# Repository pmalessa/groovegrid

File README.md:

# README #

GrooveGrid WS2812b Controller

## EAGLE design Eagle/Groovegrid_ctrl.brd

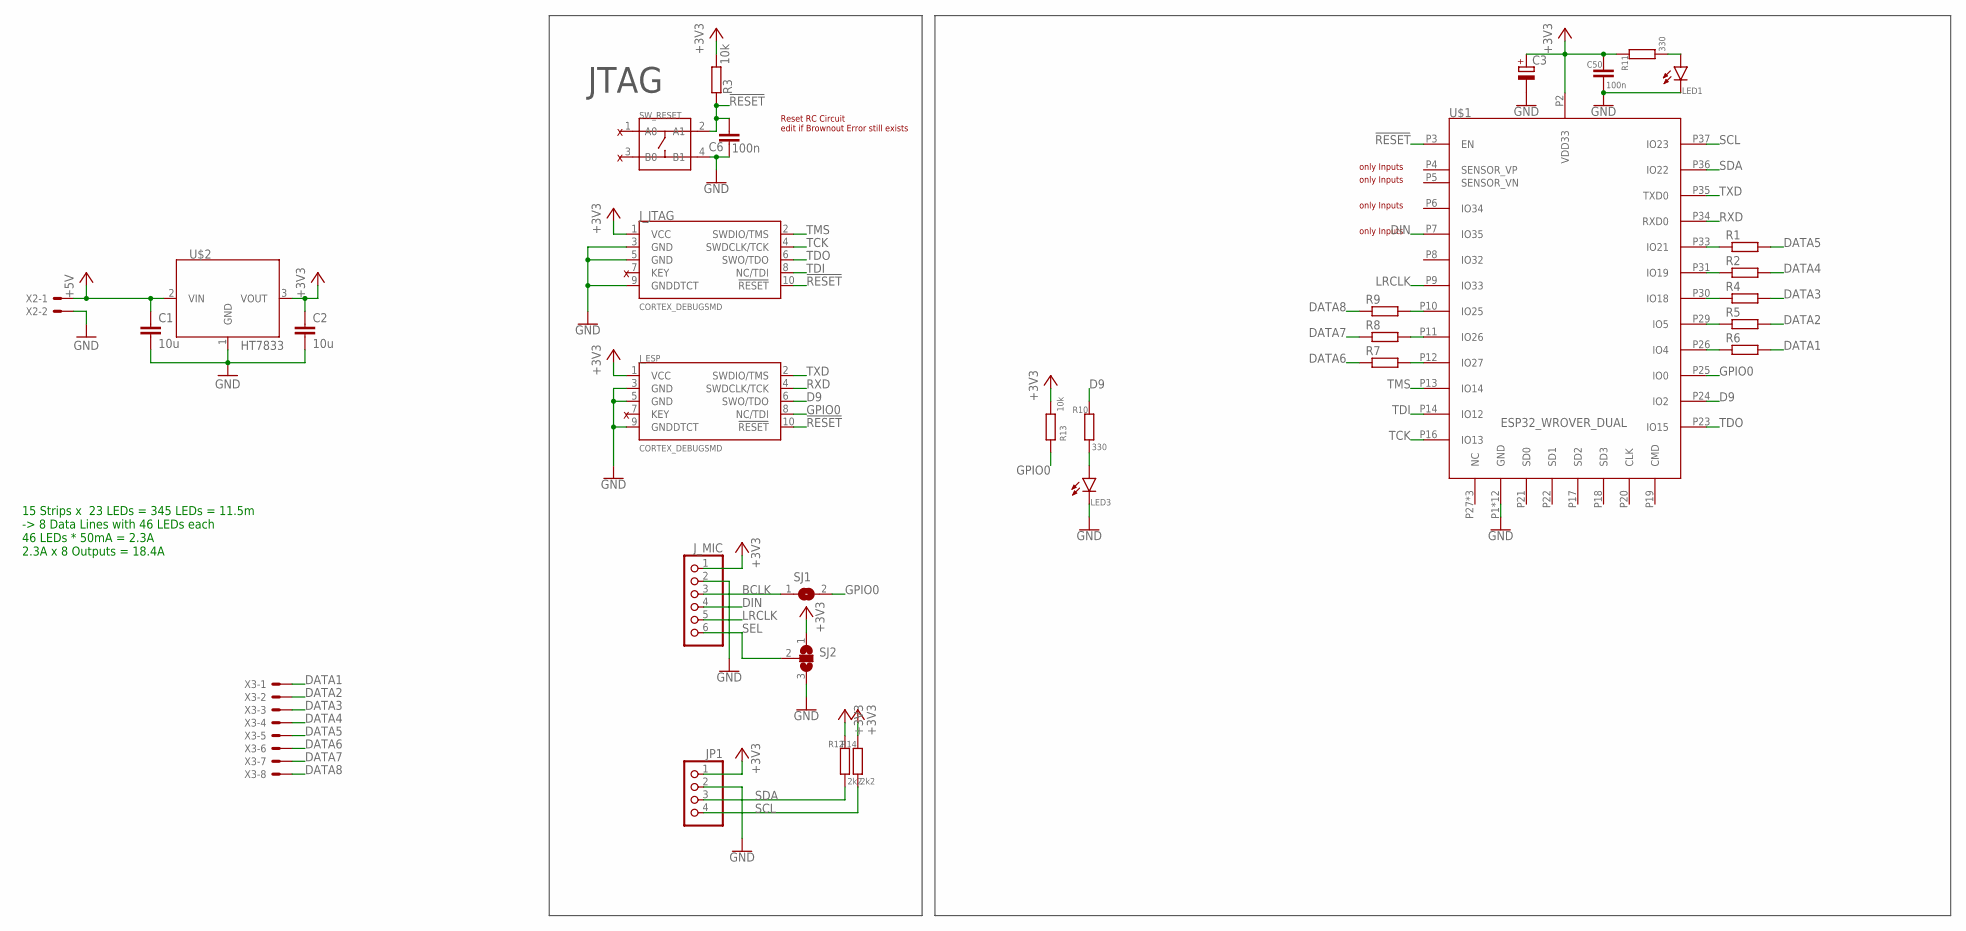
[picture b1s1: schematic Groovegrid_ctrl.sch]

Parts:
C1, C2: 10u; C0805
C3: CPOL-EUD; PANASONIC_D
C6, C50: 100n; C0805K
JP1: PINHD-1X4; 1X04
J_ESP: CORTEX_DEBUGSMD; 2X5_FTSH-105
J_JTAG: CORTEX_DEBUGSMD; 2X5_FTSH-105
J_MIC: PINHD-1X6; 1X06
LED1, LED3: LEDCHIPLED_0805; CHIPLED_0805
R1, R2, R4, R5, R6, R7, R8, R9: R-EU_R0805; R0805
R3, R13: 10k; R0805
R10, R11: 330; R0805
R12, R14: 2k2; R0805
SJ1: SJ
SJ2: SJ2W; SJ_2
SW_RESET: SKQGADE010; SW_4P-5.2X5.2X1.5MM
U$1: ESP32_WROVER_DUAL; ESP32_WROVER
U$2: HT7833; SOT150P417X160-4N
X2: JST-XH-02-PIN-ROUND-PAD; JST-XH-02-PACKAGE-ROUND-PAD
X3: JST-XH-08-PIN-ROUND-PAD; JST-XH-08-PACKAGE-ROUND-PAD

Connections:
!RESET: C6.1, J_ESP.10 (!RESET), J_JTAG.10 (!RESET), R3.1, SW_RESET.2 (A1), U$1.P3 (EN)
+3V3: C2.1, C3.+, C50.1, JP1.1, J_ESP.1 (VCC), J_JTAG.1 (VCC), J_MIC.1, R3.2, R11.1, R12.1, R13.2, R14.1, SJ2.1, U$1.P2 (VDD33), U$2.3 (VOUT)
+5V: C1.1, U$2.2 (VIN), X2.1
BCLK: J_MIC.3, SJ1.1
D9: J_ESP.6 (SWO/TDO), R10.1, U$1.P24 (IO2)
DATA1: R6.2, X3.1
DATA2: R5.2, X3.2
DATA3: R4.2, X3.3
DATA4: R2.2, X3.4
DATA5: R1.2, X3.5
DATA6: R7.1, X3.6
DATA7: R8.1, X3.7
DATA8: R9.1, X3.8
DIN: J_MIC.4, U$1.P7 (IO35)
GND: C1.2, C2.2, C3.-, C6.2, C50.2, JP1.2, J_ESP.3 (GND), J_ESP.5 (GND), J_ESP.9 (GNDDTCT), J_JTAG.3 (GND), J_JTAG.5 (GND), J_JTAG.9 (GNDDTCT), J_MIC.2, LED1.C, LED3.C, SJ2.3, SW_RESET.4 (B1), U$1.P1 (GND), U$1.P15 (GND), U$1.P38 (GND), U$1.TH1 (GND), U$1.TH2 (GND), U$1.TH3 (GND), U$1.TH4 (GND), U$1.TH5 (GND), U$1.TH6 (GND), U$1.TH7 (GND), U$1.TH8 (GND), U$1.TH9 (GND), U$2.1 (GND), X2.2
GPIO0: J_ESP.8 (NC/TDI), R13.1, SJ1.2, U$1.P25 (IO0)
LRCLK: J_MIC.5, U$1.P9 (IO33)
unnamed: R1.1, U$1.P33 (IO21)
unnamed: R2.1, U$1.P31 (IO19)
unnamed: R4.1, U$1.P30 (IO18)
unnamed: R5.1, U$1.P29 (IO5)
unnamed: LED3.A, R10.2
unnamed: R6.1, U$1.P26 (IO4)
unnamed: R7.2, U$1.P12 (IO27)
unnamed: R8.2, U$1.P11 (IO26)
unnamed: R9.2, U$1.P10 (IO25)
unnamed: LED1.A, R11.2
RXD: J_ESP.4 (SWDCLK/TCK), U$1.P34 (RXD0)
SCL: JP1.4, R14.2, U$1.P37 (IO23)
SDA: JP1.3, R12.2, U$1.P36 (IO22)
SEL: J_MIC.6, SJ2.2
TCK: J_JTAG.4 (SWDCLK/TCK), U$1.P16 (IO13)
TDI: J_JTAG.8 (NC/TDI), U$1.P14 (IO12)
TDO: J_JTAG.6 (SWO/TDO), U$1.P23 (IO15)
TMS: J_JTAG.2 (SWDIO/TMS), U$1.P13 (IO14)
TXD: J_ESP.2 (SWDIO/TMS), U$1.P35 (TXD0)

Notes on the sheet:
15 Strips x 23 LEDs = 345 LEDs = 11.5m -> 8 Data Lines with 46 LEDs each 46 LEDs * 50mA = 2.3A 2.3A x 8 Outputs = 18.4A
JTAG
Reset RC Circuit edit if Brownout Error still exists
only Inputs

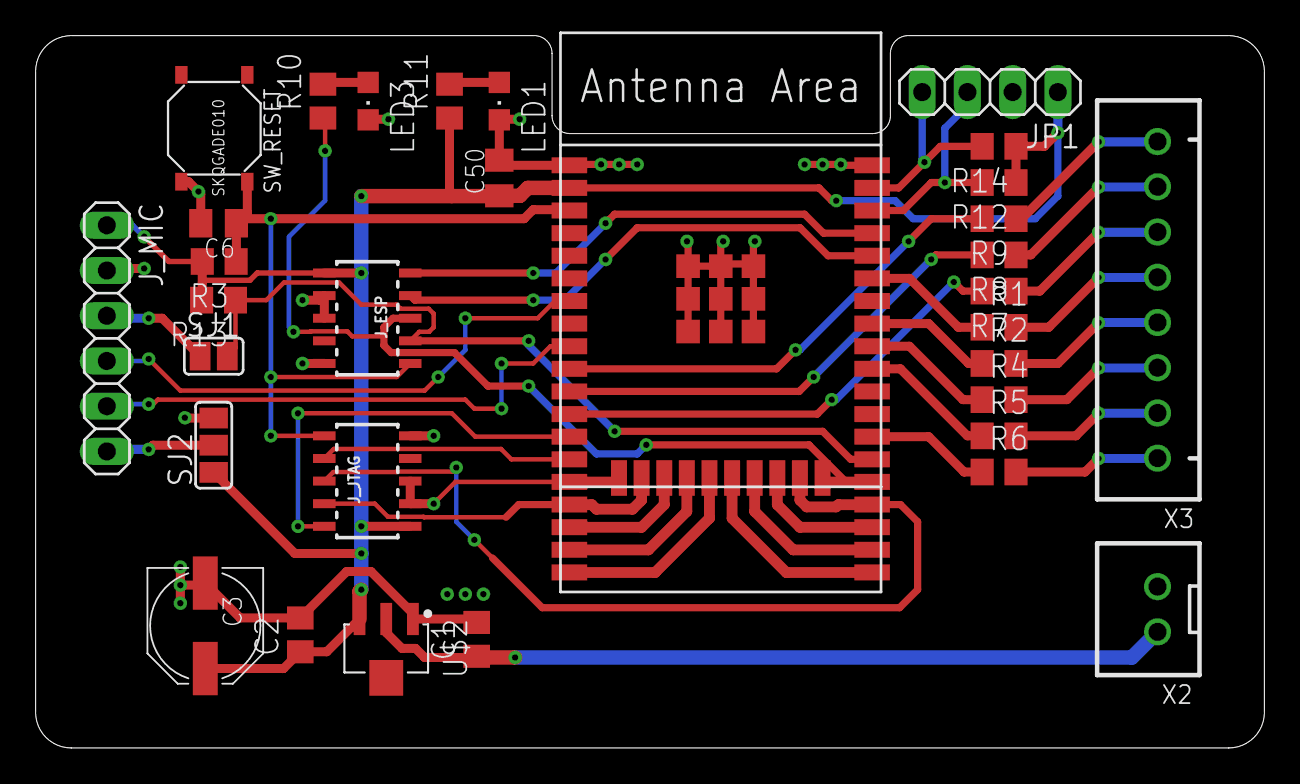
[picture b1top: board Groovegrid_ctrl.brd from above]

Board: 2 copper layers, 69.0 x 40.0 mm, 32 parts (0 on the bottom side), 36 nets.

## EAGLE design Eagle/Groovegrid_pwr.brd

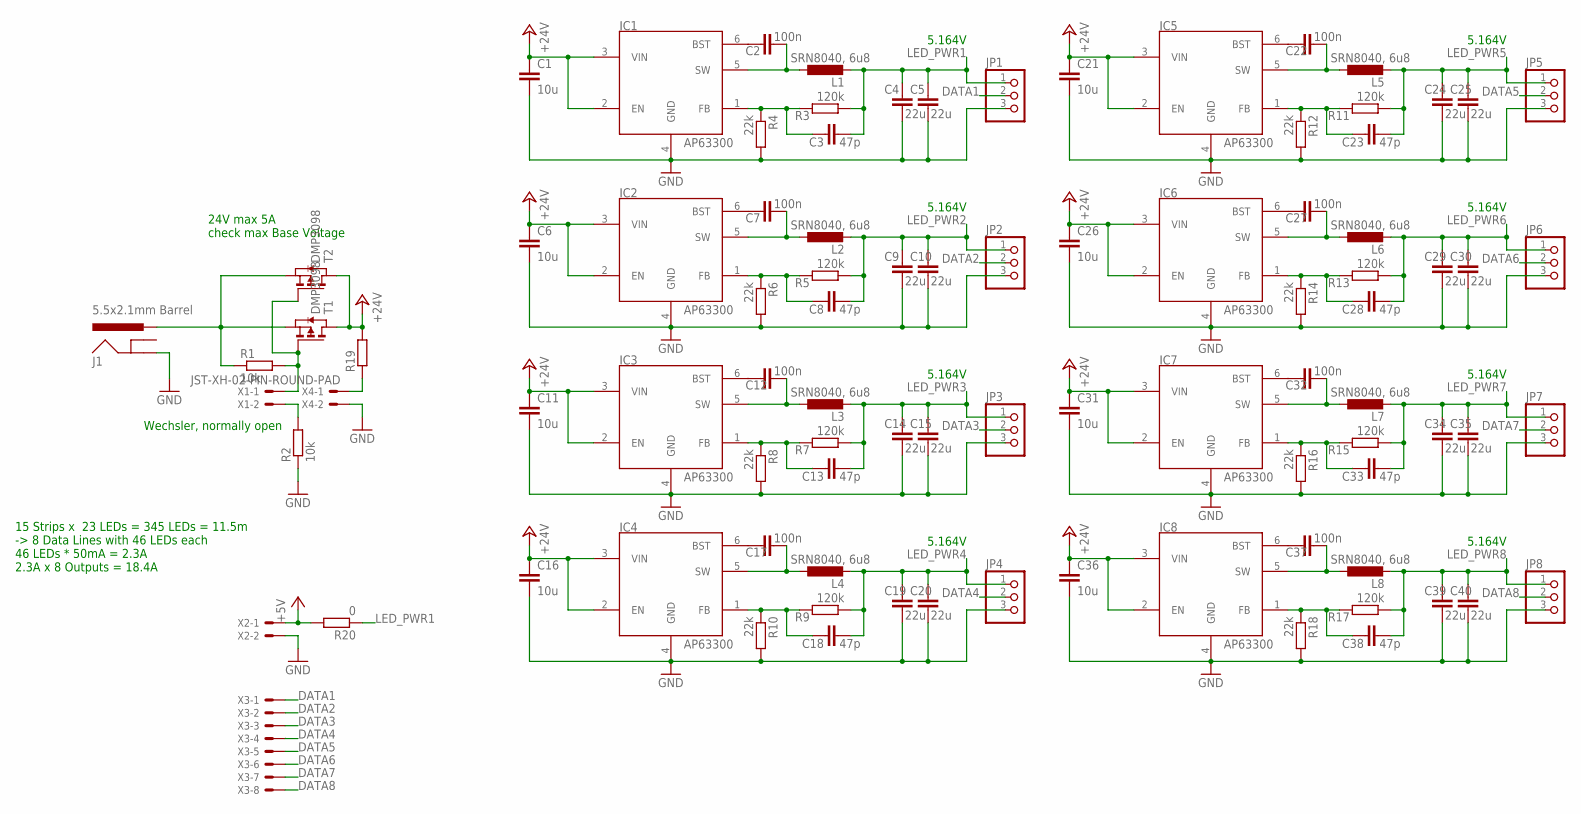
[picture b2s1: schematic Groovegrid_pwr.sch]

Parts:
C1, C6, C11, C16, C21, C26, C31, C36: 10u; C1206
C2, C7, C12, C17, C22, C27, C32, C37: 100n; C0805
C3, C8, C13, C18, C23, C28, C33, C38: 47p; C0805
C4, C5, C9, C10, C14, C15, C19, C20, C24, C25, C29, C30, C34, C35, C39, C40: 22u; C1206
IC1, IC2, IC3, IC4, IC5, IC6, IC7, IC8: AP63300; SOT23-6
J1: 5.5x2.1mm Barrel; POWER_JACK_SMD
JP1, JP2, JP3, JP4, JP5, JP6, JP7, JP8: PINHD-1X3; 1X03
L1, L2, L3, L4, L5, L6, L7, L8: SRN8040, 6u8; SRN8040
R1, R2: 10k; R0805
R3, R5, R7, R9, R11, R13, R15, R17: 120k; R0805
R4, R6, R8, R10, R12, R14, R16, R18: 22k; R0805
R19: R-EU_R0805; R0805
R20: 0; R0805
T1, T2: DMP3098; SOT23-3
X1, X2, X4: JST-XH-02-PIN-ROUND-PAD; JST-XH-02-PACKAGE-ROUND-PAD
X3: JST-XH-08-PIN-ROUND-PAD; JST-XH-08-PACKAGE-ROUND-PAD

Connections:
+5V: R20.2, X2.1
+24V: C1.1, C6.1, C11.1, C16.1, C21.1, C26.1, C31.1, C36.1, IC1.2 (EN), IC1.3 (VIN), IC2.2 (EN), IC2.3 (VIN), IC3.2 (EN), IC3.3 (VIN), IC4.2 (EN), IC4.3 (VIN), IC5.2 (EN), IC5.3 (VIN), IC6.2 (EN), IC6.3 (VIN), IC7.2 (EN), IC7.3 (VIN), IC8.2 (EN), IC8.3 (VIN), R19.2, T1.3 (D), T2.3 (D)
DATA1: JP1.2, X3.1
DATA2: JP2.2, X3.2
DATA3: JP3.2, X3.3
DATA4: JP4.2, X3.4
DATA5: JP5.2, X3.5
DATA6: JP6.2, X3.6
DATA7: JP7.2, X3.7
DATA8: JP8.2, X3.8
GND: C1.2, C4.2, C5.2, C6.2, C9.2, C10.2, C11.2, C14.2, C15.2, C16.2, C19.2, C20.2, C21.2, C24.2, C25.2, C26.2, C29.2, C30.2, C31.2, C34.2, C35.2, C36.2, C39.2, C40.2, IC1.4 (GND), IC2.4 (GND), IC3.4 (GND), IC4.4 (GND), IC5.4 (GND), IC6.4 (GND), IC7.4 (GND), IC8.4 (GND), J1.VIN-, JP1.3, JP2.3, JP3.3, JP4.3, JP5.3, JP6.3, JP7.3, JP8.3, R2.1, R4.2, R6.2, R8.2, R10.2, R12.2, R14.2, R16.2, R18.2, X2.2, X4.2
LED_PWR1: C3.2, C4.1, C5.1, JP1.1, L1.P$2 (2), R3.1, R20.1
LED_PWR2: C8.2, C9.1, C10.1, JP2.1, L2.P$2 (2), R5.1
LED_PWR3: C13.2, C14.1, C15.1, JP3.1, L3.P$2 (2), R7.1
LED_PWR4: C18.2, C19.1, C20.1, JP4.1, L4.P$2 (2), R9.1
LED_PWR5: C23.2, C24.1, C25.1, JP5.1, L5.P$2 (2), R11.1
LED_PWR6: C28.2, C29.1, C30.1, JP6.1, L6.P$2 (2), R13.1
LED_PWR7: C33.2, C34.1, C35.1, JP7.1, L7.P$2 (2), R15.1
LED_PWR8: C38.2, C39.1, C40.1, JP8.1, L8.P$2 (2), R17.1
unnamed: C7.1, IC2.6 (BST)
unnamed: J1.VIN+0 (VIN+), J1.VIN+1 (VIN+), R1.1, T1.2 (S), T2.2 (S)
unnamed: C7.2, IC2.5 (SW), L2.P$1 (1)
unnamed: R1.2, T1.1 (G), T2.1 (G), X1.1
unnamed: C8.1, IC2.1 (FB), R5.2, R6.1
unnamed: R2.2, X1.2
unnamed: C2.1, IC1.6 (BST)
unnamed: C2.2, IC1.5 (SW), L1.P$1 (1)
unnamed: C3.1, IC1.1 (FB), R3.2, R4.1
unnamed: C12.1, IC3.6 (BST)
unnamed: C12.2, IC3.5 (SW), L3.P$1 (1)
unnamed: C13.1, IC3.1 (FB), R7.2, R8.1
unnamed: C17.1, IC4.6 (BST)
unnamed: C17.2, IC4.5 (SW), L4.P$1 (1)
unnamed: C18.1, IC4.1 (FB), R9.2, R10.1
unnamed: C22.1, IC5.6 (BST)
unnamed: C22.2, IC5.5 (SW), L5.P$1 (1)
unnamed: C23.1, IC5.1 (FB), R11.2, R12.1
unnamed: C27.1, IC6.6 (BST)
unnamed: C27.2, IC6.5 (SW), L6.P$1 (1)
unnamed: C28.1, IC6.1 (FB), R13.2, R14.1
unnamed: C32.1, IC7.6 (BST)
unnamed: C32.2, IC7.5 (SW), L7.P$1 (1)
unnamed: C33.1, IC7.1 (FB), R15.2, R16.1
unnamed: C37.1, IC8.6 (BST)
unnamed: C37.2, IC8.5 (SW), L8.P$1 (1)
unnamed: C38.1, IC8.1 (FB), R17.2, R18.1
unnamed: R19.1, X4.1

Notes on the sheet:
24V max 5A check max Base Voltage
Wechsler, normally open
15 Strips x 23 LEDs = 345 LEDs = 11.5m -> 8 Data Lines with 46 LEDs each 46 LEDs * 50mA = 2.3A 2.3A x 8 Outputs = 18.4A
5.164V

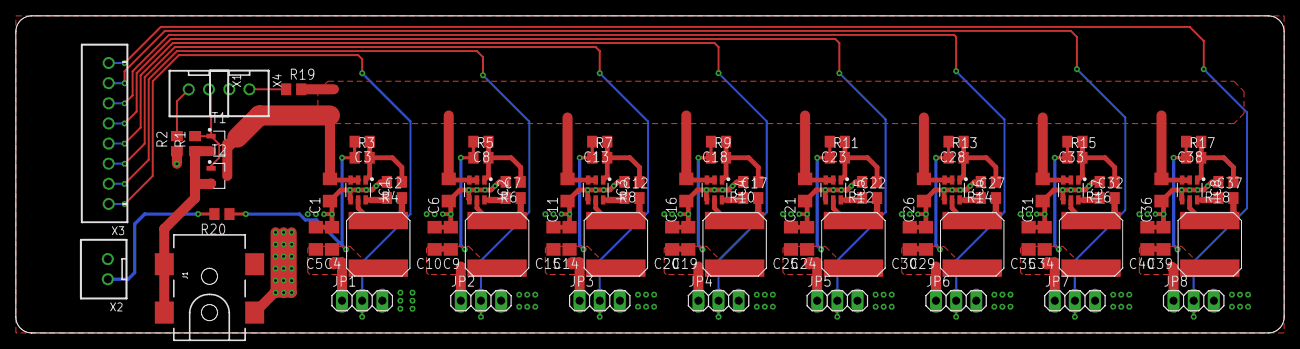
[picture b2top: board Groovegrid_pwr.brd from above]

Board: 2 copper layers, 160.0 x 40.0 mm, 91 parts (0 on the bottom side), 47 nets.

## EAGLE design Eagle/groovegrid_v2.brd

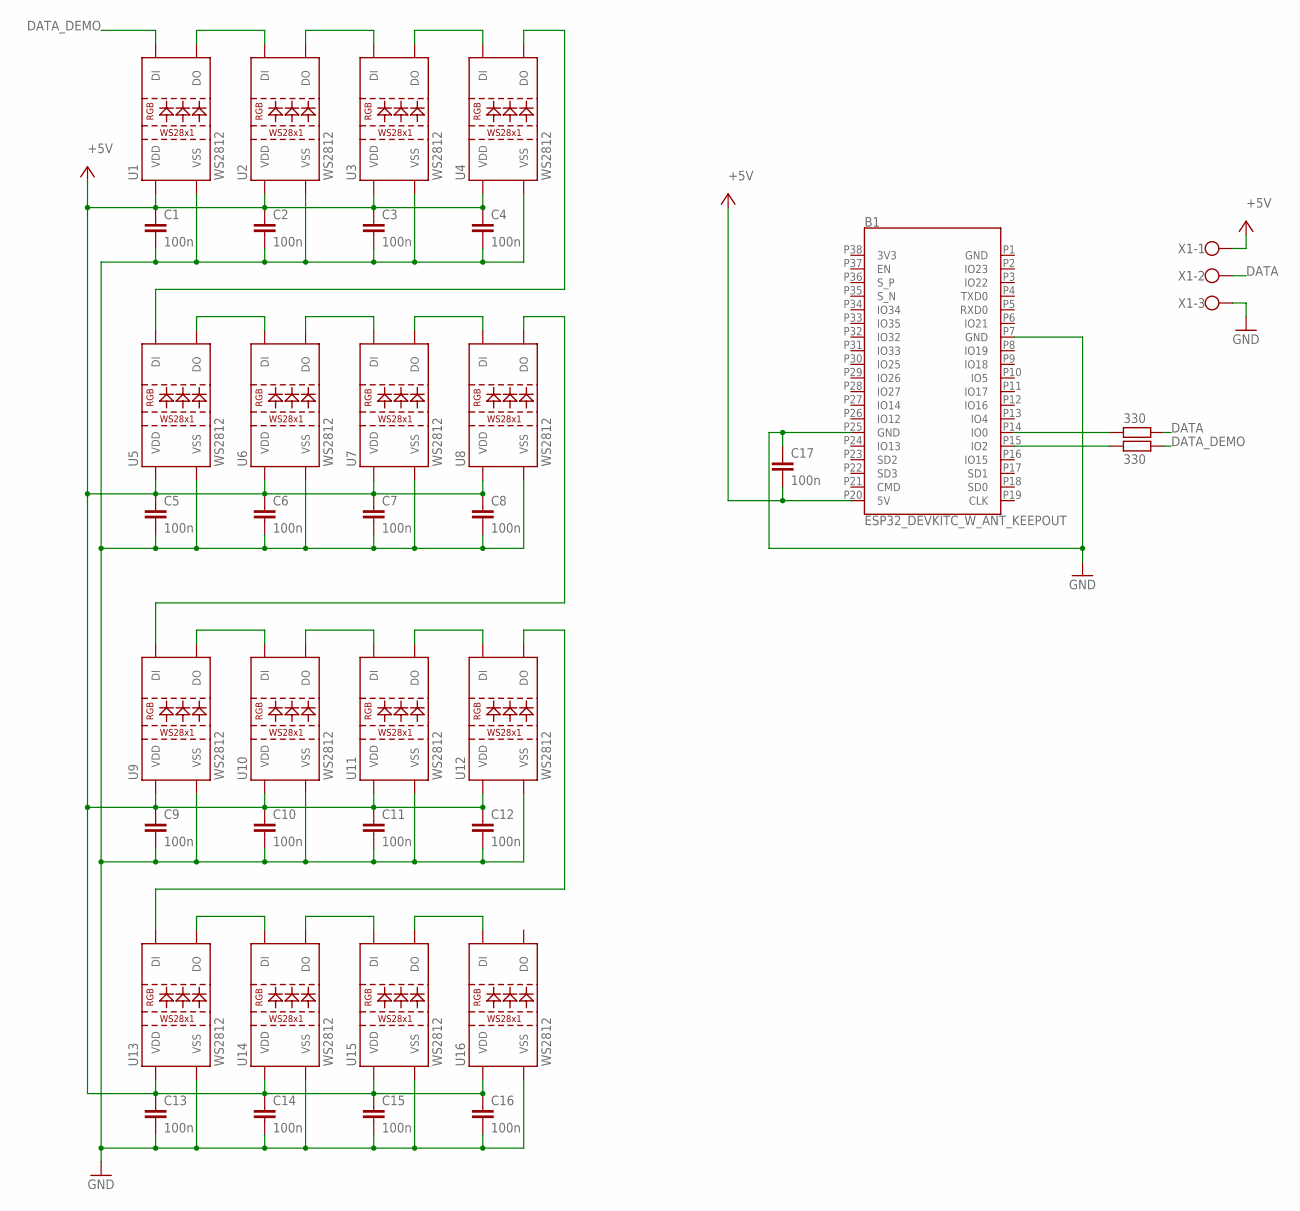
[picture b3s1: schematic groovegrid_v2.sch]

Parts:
B1: ESP32_DEVKITC_W_ANT_KEEPOUT; ESP32_DEVKITC
C1, C2, C3, C4, C5, C6, C7, C8, C9, C10, C11, C12, C13, C14, C15, C16, C17: 100n; C0805
R1, R2: 330; R0805
U1, U2, U3, U4, U5, U6, U7, U8, U9, U10, U11, U12, U13, U14, U15, U16: WS2812; LED-TRICOLOR-5050-IC
X1: W237-103

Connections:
+5V: B1.P20 (5V), C1.1, C2.1, C3.1, C4.1, C5.1, C6.1, C7.1, C8.1, C9.1, C10.1, C11.1, C12.1, C13.1, C14.1, C15.1, C16.1, C17.2, U1.3 (VDD), U1.5 (VDD), U2.3 (VDD), U2.5 (VDD), U3.3 (VDD), U3.5 (VDD), U4.3 (VDD), U4.5 (VDD), U5.3 (VDD), U5.5 (VDD), U6.3 (VDD), U6.5 (VDD), U7.3 (VDD), U7.5 (VDD), U8.3 (VDD), U8.5 (VDD), U9.3 (VDD), U9.5 (VDD), U10.3 (VDD), U10.5 (VDD), U11.3 (VDD), U11.5 (VDD), U12.3 (VDD), U12.5 (VDD), U13.3 (VDD), U13.5 (VDD), U14.3 (VDD), U14.5 (VDD), U15.3 (VDD), U15.5 (VDD), U16.3 (VDD), U16.5 (VDD), X1.1
DATA: R1.2, X1.2
DATA1: U4.1 (DO), U5.2 (DI)
DATA3: U12.1 (DO), U13.2 (DI)
DATA_DEMO: R2.2, U1.2 (DI)
GND: B1.P7 (GND), B1.P25 (GND), C1.2, C2.2, C3.2, C4.2, C5.2, C6.2, C7.2, C8.2, C9.2, C10.2, C11.2, C12.2, C13.2, C14.2, C15.2, C16.2, C17.1, U1.6 (VSS), U2.6 (VSS), U3.6 (VSS), U4.6 (VSS), U5.6 (VSS), U6.6 (VSS), U7.6 (VSS), U8.6 (VSS), U9.6 (VSS), U10.6 (VSS), U11.6 (VSS), U12.6 (VSS), U13.6 (VSS), U14.6 (VSS), U15.6 (VSS), U16.6 (VSS), X1.3
unnamed: U1.1 (DO), U2.2 (DI)
unnamed: U2.1 (DO), U3.2 (DI)
unnamed: U3.1 (DO), U4.2 (DI)
unnamed: U9.1 (DO), U10.2 (DI)
unnamed: U5.1 (DO), U6.2 (DI)
unnamed: U6.1 (DO), U7.2 (DI)
unnamed: U7.1 (DO), U8.2 (DI)
unnamed: U10.1 (DO), U11.2 (DI)
unnamed: U11.1 (DO), U12.2 (DI)
unnamed: U13.1 (DO), U14.2 (DI)
unnamed: U14.1 (DO), U15.2 (DI)
unnamed: U15.1 (DO), U16.2 (DI)
unnamed: U8.1 (DO), U9.2 (DI)
unnamed: B1.P14 (IO0), R1.1
unnamed: B1.P15 (IO2), R2.1

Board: 2 copper layers, 37 parts (0 on the bottom side), 21 nets, no tracks yet.

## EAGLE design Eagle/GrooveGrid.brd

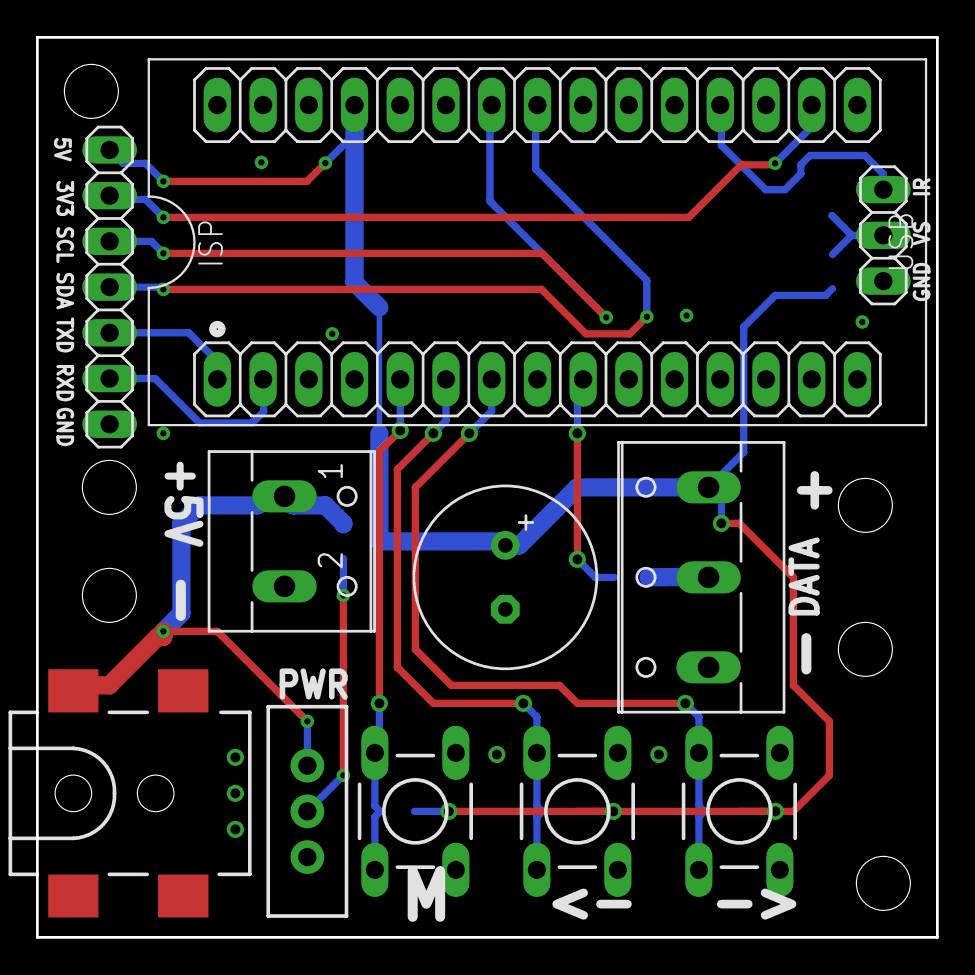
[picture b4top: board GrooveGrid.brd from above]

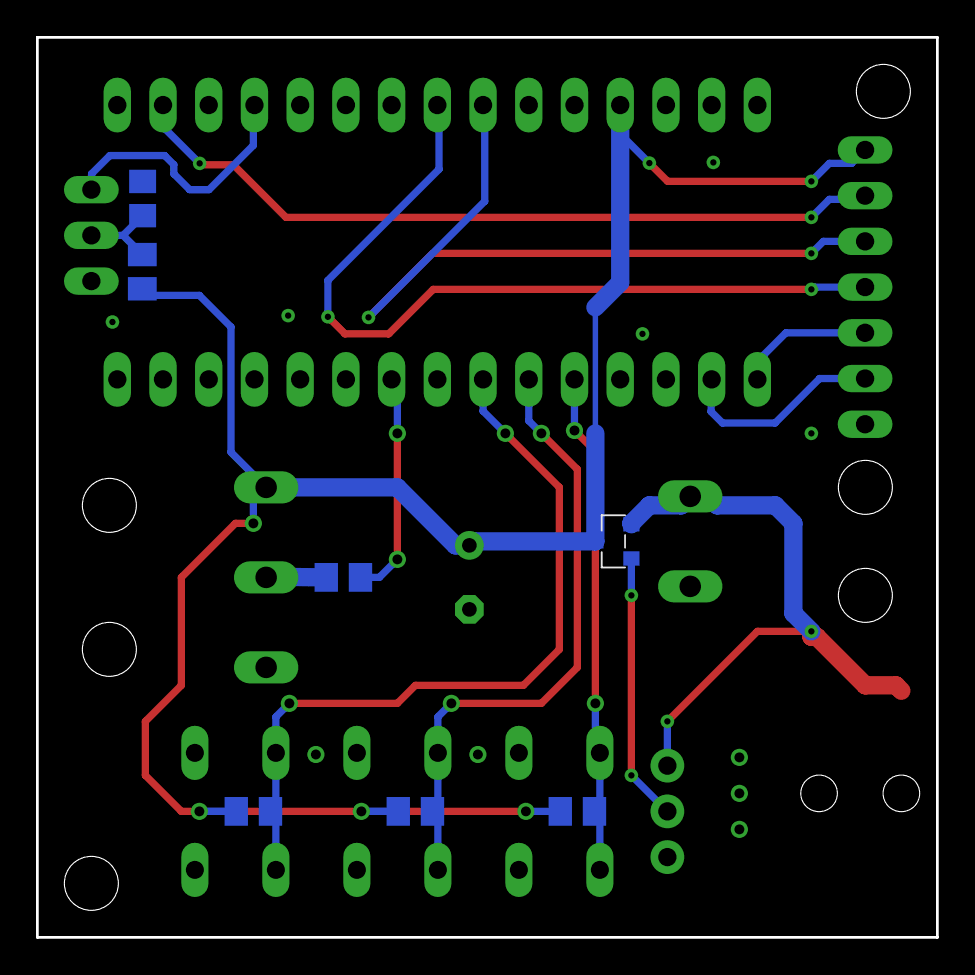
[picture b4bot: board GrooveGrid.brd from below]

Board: 2 copper layers, 50.0 x 50.0 mm, 18 parts (7 on the bottom side), 16 nets.

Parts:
C1: 1000u; E3,5-10
C2: 4u7; C0805
IR: 1X03
J1: 5.5x2.1mm Barrel; POWER_JACK_SMD
JP1: ATMEGA_NANO_MODULE
JP2: 1X07
Q1: IRLML5203; MICRO3
R1: 300; M0805
R2, R3, R4: 10k; M0805
R5: 100; M0805
S1, S2, S3: DTS-6
S5: SWITCH_SPDT_PTH_11.6X4.0MM
X1: W237-103
X2: W237-102

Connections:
3V3: JP1.17, JP2.6
+5V: C1.+, JP1.27, JP2.7, Q1.3, R2.2, R3.2, R4.2, R5.2, X1.3
BUTTON1: JP1.7, R2.1, S1.1, S1.2
BUTTON2: JP1.6, R3.1, S2.1, S2.2
BUTTON3: JP1.5, R4.1, S3.1, S3.2
DATA: JP1.9, R1.2
DC_IN: J1.VIN0, Q1.2, S5.3, X2.1
GND: C1.-, C2.2, IR.1, J1.GND, J1.P$4, JP1.4, JP1.29, JP2.1, S1.3, S1.4, S2.3, S2.4, S3.3, S3.4, S5.1, X1.1, X2.2
IR: IR.3, JP1.19
unnamed: C2.1, IR.2, R5.1
unnamed: R1.1, X1.2
unnamed: Q1.1, S5.2
RXD: JP1.2, JP2.2
SCL: JP1.24, JP2.5
SDA: JP1.23, JP2.4
TXD: JP1.1, JP2.3

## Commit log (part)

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2017-09-29 README.md created online with Bitbucket
2019-01-04 initial commit of groovegrid_v2
2019-01-04 removed LED code to LED file
2019-01-05 abstracted the LED code from the rest
2019-01-05 InitializeBoard done
2019-01-05 Left move completely done
2019-01-05 rewritten GameState Class so that it is properly declared in header file
2019-01-05 WORKING!!! HOMOS!!
2019-01-05 random now
2019-01-05 Move Down Test
2019-01-05 working version, somewhat cheatable :P
2019-01-12 spawn fix
2019-01-17 Simple Swipe detection using built-in functions is now implemented. There are still problems with detecting the correct direction, will probably have to implement swipe detection myself.
2019-01-17 Tab Bar added
2019-01-18 Horizontal Prototype for an interface for controlling animations and games
2019-01-18 Header changed
2019-01-19 remove unneccessary draw
2019-01-19 add pulsing animation
2019-01-19 Last selected Bluetooth device is now saved for session
2019-01-20 Refactoring
2019-01-20 New Implementation for GamesListView, startup commands can now be sent to GrooveGrid when Game is tapped in list
2019-01-20 Currently running game is now highlighted
2019-01-20 New common GrooveGridApp class that should be superclass of GrooveGridAnimation and GrooveGridGame. GrooveGridAnimation is already a subclass.
2019-01-20 If the running Application is a game, a floating action button is displayed on the home view, the fab is not visible if an animation is running or or nothing is running
2019-01-25 Reorgamized code
2019-01-26 Removed unused code
2019-01-26 AnimationsListView now uses BLoC pattern
2019-01-29 State incorporated into BLoC class
2019-01-31 Custom BLoC implemenatation for GlobalBloc class, other BloCs still use third party library
2019-01-31 Third party BLoC library removed from project
2019-01-31 Created central ControlsView widget to create ControlsViews of the right type
2019-01-31 New BluetoothService class that delegates to FlutterBluetoothSerial
2019-01-31 Bluetooth Connection State changes are now handled through the ConnectionBloc class
2019-02-06 Comments
2019-02-22 Changed Interface for BLoC classes. MapEventToState now returns a Set of sinks to notify and a State.
2019-02-27 speed up game a little
2019-02-27 renamed to groovegrid v2
2019-03-20 cleanup gitignore
2019-03-20 adding readme abstracting AVR specific libraries to support multi platform code (COMM for Communication/Serial and TIMER for Timer) As the Button and Timer library had to be changed to support multi 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
2019-03-20 disable Buttons for now as they are not connected
2019-03-20 restructuring in folders
2019-03-21 Starting Dark Color UI for App
2019-03-21 Grid is now OOP!! :):)
2019-03-22 New Custome GridTheme that holds theme data not present in standard Flutter Themes. GridTheme data gets passed down the widget tree via Inherited Widget.
2019-03-22 ported to Grid functions Still some errors with the Singleton Approach, PLEASE FIX CHRIS! :P
2019-03-22 fixed Grid issue, one static keyword too much. Added a static reference to each function, that calls the grid. This is necessary, as otherwise multiple global instances would exist. Hopefully not res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
2019-03-23 Made Platform defines device specific instead of architecture
2019-03-23 uploaded EventManager/Listener Pattern, not used yet
2019-03-23 fixed AVR Bug, Caling Drawboard before initializing
2019-03-23 CardTheme added with the new Flutter 1.2 API. Now requires Flutter 1.2
2019-03-23 Shadow working like in the Figma Design
2019-03-24 Started common Widget for Game and Animation List Tiles
2019-03-24 Removed unused ListTile code
2019-03-24 Gradient Background added to highlighted cards
2019-03-24 FAB with diamond shape
2019-03-25 Working Notch in Bottom Nav Bar. Still circular and no specifiable margin
2019-03-25 implemented an EventManager in c++
2019-03-25 renamed GRID to Grid implemented a Event based timer system, not done yet
2019-03-26 Added new ui_test_main.dart file that can be used to start the app with the uiTest property set to true.
2019-03-26 ui_test_main now runs the app with more animations to allow for scrolling
2019-03-26 set counter volatile, just in case...
2019-03-27 Animations view is now constructed using AppsListView
2019-03-27 Tabs now get generated lazily
2019-03-27 implemented Vector myself to support AVR, which doesnt have stl implementation fixed a few AVR Compilation bugs running on AVR now
2019-03-27 Fully functioning bottom nav bar notch integrated with all functions of the app
2019-03-27 Restart Groovegrid App button added to SwipeControlsView
2019-03-28 implemented InputListener, every App that wants to get Input Data has to inherit from it. Removed Input Handling from Inside App
2019-03-28 New MessageBloc that is used by SwipeControlsView to send messages via Bluetooth.
2019-03-28 MessageBloc now listens to incoming bluetooth serial messages
2019-03-28 Moved creation of games and animations to GrooveGridAppsBloc so state no longer depends on Bluetooth for the start and stop command functions
2019-04-04 removing (for now) unnecessary function stubs from the AppDefinition Adding UNUSED define to remove "unused var" warnings
2019-04-05 rename to RandomRectAnimation removing "non virtual dest." warning from InputListener
2019-04-05 using example server code
2019-04-05 tested AnimationRunner. Fixed Animation Times. Bluetooth Comm works as expected, ready for release.
2019-04-07 MainLoop created, compiles on both platform, now testing
2019-04-08 Creating DisguiseGame - It´s the all red display with the occasional white flash not done yet
2019-04-11 char is defined unsigned in ESP32 compiler, therefore using int. removed unused warning
2019-04-11 make the GrooveApp responsible for the initialization of its GridTile pointer by using a contructor. Therefore each App needs to call the GrooveApp constructor, mostly by calling their childs
2019-04-13 Adding a DeltaTimer
2019-04-14 using DeltaTimer in each Animation
2019-04-15 uploading FastLED_NeoMatrix, a port of the NeoMatrix Library which uses FastLED as Backend. Data Pin had to be changed to support RMT hardware. Works flawlessly, maybe some cleanup necessary
2019-04-15 fixing serial input on ESP32, Can be controlled via micro usb cable serial console now
2019-04-16 working!
2019-04-22 implemented nested classes instead of the junky code before
2019-04-24 continued fixing, adding some restructuring notes
2019-04-26 Renamed BluetoothService to GrooveBluetoothService
2019-04-28 adding virtual start and stop function to GrooveApp merging the games in Mainloop to one game pointer reset reimplemented by destroying and recreating game object
2019-04-28 removing PLATFORM definition from PLATFORM.h one has to create a CONFIG.h after cloning to select the platform. CONFIG.h is ignored to not check it in
2019-04-28 changed and therefore fixed the 2048 coordinate system. origin in topleft corner with x to the right und y to the bottom.
2019-04-28 made GameState dynamic only draw on a square GridTile. If its a rect, take the largest possible square in it
2019-04-28 adding fillScreen function to clear Tile
2019-04-28 moving DeltaTimer to GrooveApp Class, therefore all Apps have a DeltaTimer Porting 2048 to use DeltaTimer
2019-04-28 renamed XMAX and YMAX to WIDTH and HEIGHT, as it makes more sense fixing adafruit_gfx range
2019-04-29 FlappyGroove working
2019-04-30 uploading SpectrumAnimation, but too slow changed rand() to esp_random() for true Hardware Random Gen
2019-04-30 Collision detection works and stops the game, but player can continue afterwards.
2019-04-30 uploading a first draft of a protocol specification
2019-04-30 rewritten AnimationRunner to use a list as an animationQueue to support phone Communication later. using a vector instead of queue to support repetition
2019-04-30 command block spec
2019-05-02 adding function new_instance(). Each GrooveApp has to implement it to be able to create a new object of the same type without knowing the type. This is necessary to reset the current App by deleting 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
2019-06-01 added measurements of data packets
2019-06-07 removed FastLED_NeoMatrix and merged its functionality (2D to 1D translation) to Grid
2019-07-07 port of ColorPalette Animation works on table, still some flickering changed back to 30fps added fromCRGB function to convert color type
2019-07-08 adding a separate writePixel function to support CRGB colors directly without conversion moving the render loop to a separate thread
2019-07-08 adding FastLED.show () to endless loop instead of calling dynamically uploading FastLED master branch, as config file had to be changed changed FastLED config RMT Channels to 1 -> seems to fix flicker
2019-07-09 "fixing" ColorPalette Animation to display crosses again
2019-07-09 removed 16bit Adafruit Color, all 32bit CRGB color now
2019-07-10 implementing JSON onCommand in all Apps removing all the multiApp nonsense in MainLoop
2019-07-18 fixing shifted Grid on table
2019-08-02 Refactoring and comments...
2019-08-09 adding NFSAnimation
2019-08-17 adding Microphone Driver and SpectrumAnimation
2019-09-05 fixing FlappyGroove
2019-09-14 implemented animationMap, working on board
2019-09-14 same with AnimationMap
2019-09-18 removing TaskScheduler, replacing with preemptive Task Scheduler by FreeRTOS. Therefore, Task run in an endless loop with a vTaskDelay to feed the watchdog. This enables decoupling from Framerate lat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
2019-09-27 Revert "removing TaskScheduler, replacing with preemptive Task Scheduler by FreeRTOS."
    This reverts commit 7743b5e2aa2d3e3b46e89adb7043934113020b96.
2019-09-28 rewritten onCommand function. a CommandMsg pointer is now passed to the CommInterfaces. Response Doc is inside of it. Therefore there is no need to create the rspDoc by the app itself.
2019-09-29 Replaced Serial print with ESP_LOG, removed arduinoFFT and SPI depencency, replaced timer implementation with FreeRTOS function, BLE Arduino HAL has to be ported as well
2019-10-04 small fix
2019-10-05 some sdkconfig corrections
2019-10-06 adding jlink as debugger, uploading "working" sdkconfig, disabling FastLED for now as it is just using bitbang GPIO instead of RMT, adding partition.csv, not used yet. downgraded esp-idf to v3.2
2019-10-09 adding partition table updating ESP-IDF to v3.3 again, as there is a bugfix for INT WDT Timeout in BT Stack check for new sdkconfig stack sizes necessary
2019-10-09 move partition to root folder
2019-10-10 removing TaskScheduler, as it was just running the app. Adding an appTask to MainLoop to let the IdleTask be an idle Task.
2019-10-10 removing the reset function as we now know the name of the app thats running. Therefore its just a "start" of the same app
2019-10-12 removing Sloeber folder structure, long live gridOS :)
2019-10-15 BLE library updated to 1.0.4
2019-10-16 Fixing onDisconnect erase function. Simplifying JSON API, no connect command anymore. The app just has to ask for its userID and maybe the other userIDs
2019-10-18 Let the App be the only one on the App core to avoid flickering
2019-10-19 creating Battleship game. Main screen and ship/crosshair working, needs coordinate cleanup
2019-10-19 simplify SpectrumAnimation, turning it into fake first
2019-10-19 adding reset to DeltaTimer
2019-10-19 fixing DeltaTimer reset
2019-10-19 adding RandomCircleAnimation
2019-10-19 refactoring playerID to 0..1 fixing Player 3/4
2019-10-30 fixing BLE debug build
2019-10-31 fixing shootAnimation of Battleship adding checkWin function to Battleship
2019-10-31 Adding BootAnimation decreasing Boot Delay
2019-12-01 adding arduinoFFT library, as includes had to be added. adding microphone fft, doesn´t look very good... removeing debug mode from battleship
2019-12-15 update 3D
2019-12-16 cleaning up Microphone code changed to long incremental mean. added attack/release peak detection for microphone samples
2019-12-22 adding ShotAnimation removing TicTacToe fixing 2048 removing new_instance function as it is not necessary because of AppMap
2019-12-24 fixing some Animations
2020-03-07 uploading recent files
2020-04-28 adding version info, as newest platform version is not compatible
2020-08-12 cleanup
2020-10-27 RGBW support working. WalkingDot Animation added
2020-11-01 - switched to OTA partition scheme - replaced Boot Animation by Gg
2020-11-14 moved from BLE Communication to HTTP GET/POST commands with mDNS Service Discovery
2020-11-14 removed all warnings
2020-11-16 First version of Provisioning implemented. Works with ESP Provision App.
2021-01-02 implemented SPIFFS into Storage class renamed setValue to setConfig removed sdkconfig.h, not used
2021-01-16 - rewritten Grid and MessageService as static classes
2021-01-18 - rewritten MainLoop without multipleAppSupport and as a static class - rewritten MesssageCallbacks as registering functions by the App itself - moved some includes to PLATFORM.h - moved AppMap and A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
2021-12-05 - back to bluetooth version

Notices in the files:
parts and their libraries:
SparkFun-Connectors: Licensing: Creative Commons ShareAlike 4.0 International - https://creativecommons.org/licenses/by-sa/4.0
